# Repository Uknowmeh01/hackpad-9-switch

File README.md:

# **Uknowmeh01 project**

## **macropad  switch**

i did this project it my first one ever so i try to did something easy and practical you can plug it in USB C and each punch do something 
exemple:1-for changing song  2-pause/start 3- changing to the previous song 4-for changing the desk in the left 5-to create a new desk 6-change desk to the right 7-change led 8-do a screenshot 9-shuting down the rotator-change the volume it will be a plug and play 

## **design**

i designed it with a rotator and 9 switch i wanted something perfect the case it's designed for a maximum of space for cables but a minimaliste look it why it have  specific shape

**warning:ishearshe all the price in amazon french it can be lower in another shop**

|number|the product name|the link|the price|
|-|-|-|-|
|0.|a power supply 850w|https://www.amazon.fr/gp/product/B0FJWGYXZK/ref=ox\_sc\_act\_title\_1?smid=A3T0O12NRI0MR5\&th=1|76.91€|
|1.|a boxe of 10 cherry MX switch|https://www.amazon.fr/Topiky-M%C3%A9canique-Commutateurs-Interrupteur-Remplacement/dp/B086MQXQW7/ref=sr\_1\_6?\_\_mk\_fr\_FR=%C3%85M%C3%85%C5%BD%C3%95%C3%91\&crid=3LXQS8UQWH8GS\&dib=eyJ2IjoiMSJ9.wT3dGkj9ALLw75ZeRZPNgOXlycN4y2EqJwBCu3XOt7JB4T7CkcS9NZWaXVGWZijHpjVgfhV9Qjlqhwf008GaDkdapDO92w5X2WUVA503RZ0rZ6C3XqHYoLCr6\_prk4s2gTJAEnnIrm2OM8xiXqu4DcoP53gSfBSW-YaBfg8oe6RWJoSdjEoSUCJ1xPuY\_uPnfncHK7d7wLGAWSuUiiRR-rlH5pJJDBeMgbMYdwCFIaki\_LzYHVpRuhJRP7Xud-h1aEo1zft36d1IN2TVpB-Pmf4r-sssqZ0Vluxo5cJ6t-I.8qnz2u78z1qM\_PEwMtDMY50-rqzSYPe35gpBmUGDs6w\&dib\_tag=se\&keywords=a+boxe+of+10+cherry+MX+switch\&qid=1773503591\&sprefix=a+boxe+of+10+cherry+mx+switch%2Caps%2C607\&sr=8-6|14.99€|
|2.|5 rotator encoder+cables|https://www.amazon.fr/WMYCONGCONG-dencodeur-rotatifs-multicolores-sauteuse/dp/B07FJQH1F7/ref=sr\_1\_12?\_\_mk\_fr\_FR=%C3%85M%C3%85%C5%BD%C3%95%C3%91\&crid=1X05YR20RR2R5\&dib=eyJ2IjoiMSJ9.uSEWgUFfOrthLaTKFyhWsO0UAaiyVPDAVZ0QlW057ZaQMVjaIbJ1CsV3tE70DRcsnHVPmYw-mY\_NolDlwMORfoMJjhgHU2-GN0AVMFU\_0yfapyQjxicdbfYxO-W-Su\_wLohjljE-QSxWX9VyvXvI2-x2UB0-BCwLfY8rZ9ziyHBmg8BRTC5bnqMZIqtAGk4o83c9fv-OqiTux-t6XGNKOyBbZU7zTWbL6tIfuZW0brnsaWfaj65HGl9r1gfsrB5fHbpQx-7hKd5XAJZDJlI0OkPg0UzXzydBCh\_emiQ5mBs.1XoWMZXXtMvn4CLEyzt2gs2syVDIRzRkKzS39tpvzS0\&dib\_tag=se\&keywords=3+rotator+encoder\&qid=1773503532\&sprefix=3+rotator+encoder%2Caps%2C328\&sr=8-12|12€|
|4.|1.75mm PLA Printer Filament|https://www.amazon.fr/GEEETECH-Filament-1-75mm-Imprimante-Spool/dp/B071DM81ZK/ref=pd\_bxgy\_thbs\_d\_sccl\_1/521-5091465-6196349?pd\_rd\_w=b7CCC\&content-id=amzn1.sym.3241dc27-b429-4dd8-b1d4-32e571df604c\&pf\_rd\_p=3241dc27-b429-4dd8-b1d4-32e571df604c\&pf\_rd\_r=7JC2WV4QCZ0ZRXQG54ED\&pd\_rd\_wg=McbXX\&pd\_rd\_r=5b287750-bf16-4036-be8f-f73282c57b11\&pd\_rd\_i=B071DM81ZK\&th=1|18.04€|
|5.|Seeed Studio XIAO ESP32|https://www.amazon.fr/Seeed-Studio-ESP32C3-charge-Arduino/dp/B0B94JZ2YF/ref=sr\_1\_3\_mod\_primary\_new?dib=eyJ2IjoiMSJ9.jMlQaRW80lkonFMSZSqEaQ89bGX68RWRS2lUYQuFgaJw5cZlC8GbmM3SlSdchfPyHHkyAluuHNIN4QY4UiXRNOMjtWXe4xcxw69yNs3QxcEb3XDuXfO2WFoGDSto6IxKFLGjzkUNEbnWkM9EBXiDBZaaCplUQzPd8ae2nGFzyGGJDAZ2yFe8IVoBTPpF8dQ9Q449eMdYwAuzt-l7sQ6gD5EP--buGzSS1canbW8KOPcADnYzTjPXgyZRSnXit5TsEDrL-ugoz8ZuYx6kC2\_UdY1XSAP4-0Nmh1TKL2fIFWA.rxoiE2VRyU9xEGhji3RIgVeYkItA-Xuro0WH0rZI15Y\&dib\_tag=se\&keywords=Seeed%2BStudio%2BXIAO%2BESP32\&qid=1773503417\&sbo=RZvfv%2F%2FHxDF%2BO5021pAnSA%3D%3D\&sr=8-3\&th=1|25.03€|
|6.|3d printer|https://www.amazon.fr/Adventurer-Nivellement-Automatique-Refroidissement-220%C3%97220%C3%97220mm/dp/B0CH9K2KWQ/ref=sr\_1\_9?th=1|248.99€|
|TOTAL|-------||388.87€|

Note: the 850W power supply is for my PC and my 3D printer, not for the macropad.
my parents did the sanity check

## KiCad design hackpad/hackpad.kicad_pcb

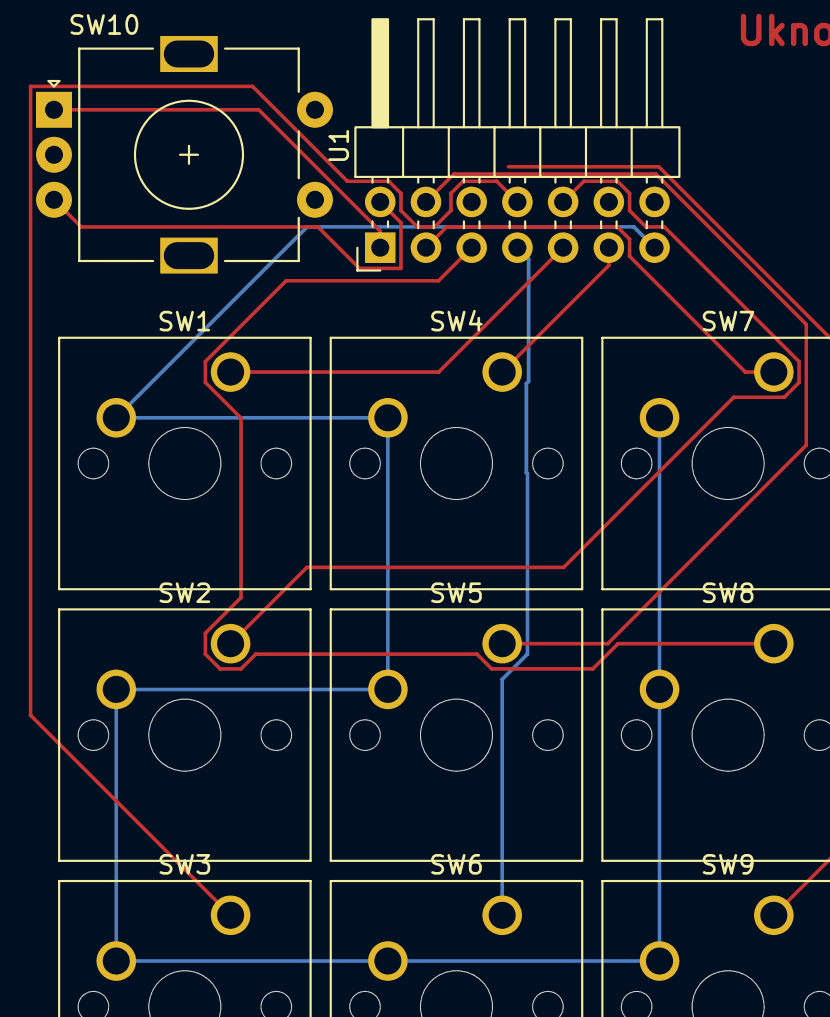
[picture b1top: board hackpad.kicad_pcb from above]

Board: 2 copper layers, 11 parts (0 on the bottom side), 11 nets.

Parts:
SW1, SW2, SW3, SW4, SW5, SW6, SW7, SW8, SW9: SW_Push; SW_Cherry_MX_1.00u_PCB
SW10: RotaryEncoder; RotaryEncoder_Alps_EC11E-Switch_Vertical_H20mm
U1: SeeeduinoXIAO; PinHeader_2x07_P2.54mm_Horizontal

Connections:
GND: SW1.2, SW2.2, SW3.2, SW4.2, SW5.2, SW6.2, SW7.2, SW8.2, SW9.2, U1.13 (GND)
unnamed: SW10.A, U1.1 (PA02_A0_D0)
unnamed: SW10.B, U1.2 (PA4_A1_D1)
unnamed: SW1.1, SW2.1, U1.9 (PA7_A8_D8_SCK), U1.10 (PA5_A9_D9_MISO)
unnamed: SW4.1, U1.11 (PA6_A10_D10_MOSI)
unnamed: SW8.1, U1.5 (PA8_A4_D4_SDA)
unnamed: SW9.1, U1.6 (PA9_A5_D5_SCL)
unnamed: SW7.1, U1.3 (PA10_A2_D2)
unnamed: SW5.1, U1.4 (PA11_A3_D3)
unnamed: SW6.1, U1.7 (PB08_A6_D6_TX)
unnamed: SW3.1, U1.8 (PB09_A7_D7_RX)

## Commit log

2026-03-07 fusion 360 files
2026-03-10 README.md
2026-03-10 firmwar
2026-03-10 Create 3d project
2026-03-16 Rename plate-2026-03-07T13_07_28.964Z.stp to hackpad.stp
2026-03-16 Create librairie
2026-03-16 Rename firmwar to main.py
2026-03-16 Creat
2026-03-16 Create CAD
